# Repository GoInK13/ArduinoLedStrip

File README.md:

# ArduinoLedStrip
Arduino PCB to control LED strip RGB, addressable or not, with 1 IR remote, 1 pot and 2 push buttons.

**Kicad information**
This project is made using KiCad Version: 4.0.7-e2-6376~58~ubuntu14.04.1.

**Arduino information**
You need the library "RobotIRremote" in your libraries folder. I also modified "TDK2" to "12" in my arduino-1.6.9/libraries/RobotIRremote/src/IRremoteTools.cpp file.

**Component list**
The Arduino used is an ATmega328P Nano V3.
The DC 12V connector is a 5.5mm×2.1mm DC Power Supply Female Jack Socket.
The 6 transistors used are IRFZ44N Transistor N-Channel.
The polarized power capacitor is a 10µF, with a diameter egal to 8.0mm, and a pitch of 3.5mm.
SW1 and SW2 are Push Button DIP P4.
The potentiometer is a PTV09A from Bourns.
The IR receiver is a TSOP4838.
All pin header used have a pitch of 2.54mm.
All resistors are 0603 handsoldering (1kΩ).
Wemos : D1 mini

**Thanks**
Thanks to jerome-labidurie on GitHub for his d1_mini library. (Wemos)
https://github.com/jerome-labidurie/d1_mini_kicad.git

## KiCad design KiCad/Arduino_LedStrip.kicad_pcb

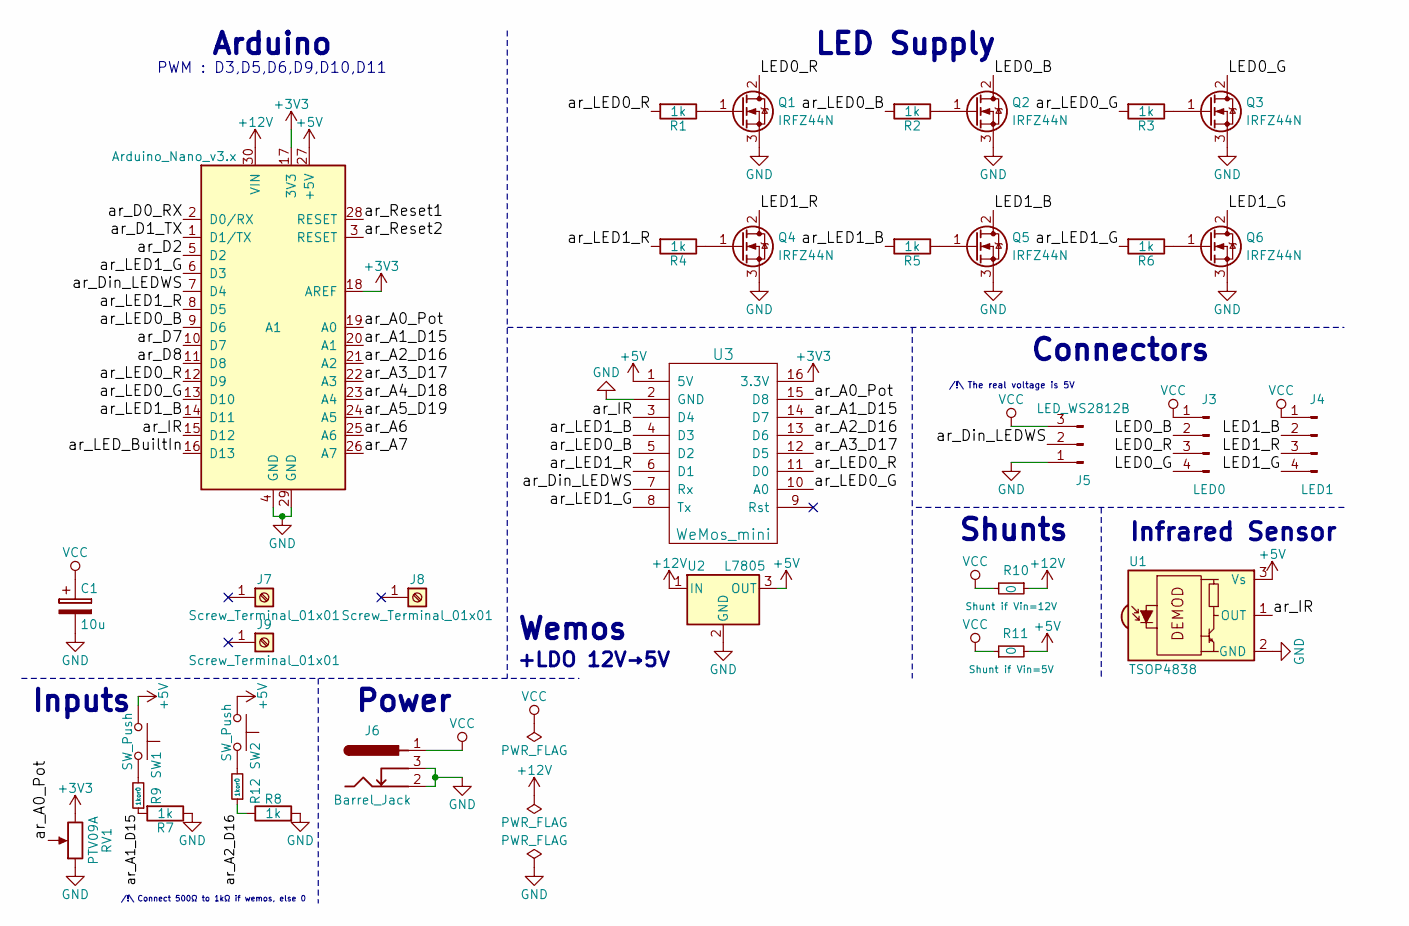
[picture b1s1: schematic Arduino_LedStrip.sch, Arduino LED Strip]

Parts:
A1: Arduino_Nano_v3.x; Arduino_Nano
C1: 10u; CP_Radial_D8.0mm_P3.50mm
J3: LED0; Pin_Header_Angled_1x04_Pitch2.54mm
J4: LED1; Pin_Header_Angled_1x04_Pitch2.54mm
J5: LED_WS2812B; Pin_Header_Angled_1x03_Pitch2.54mm
J6: Barrel_Jack; BARREL_JACK
J7, J8, J9: Screw_Terminal_01x01; MountingHole_3.2mm_M3
Q1, Q2, Q3, Q4, Q5, Q6: IRFZ44N; TO-220-3_Vertical
R1, R2, R3, R4, R5, R6, R7, R8: 1k; R_0603_HandSoldering
R9, R12: 1kor0; R_0603_HandSoldering
R10, R11: 0; R_Shunt
RV1: PTV09A; Potentiometer_Bourns_PTV09A-1_Horizontal
SW1, SW2: SW_Push; SW_PUSH_6mm_h13mm
U1: TSOP4838; IRReceiver_Vishay_MOLD-3pin
U2: L7805; TO-220-3_Vertical
U3: WeMos_mini; D1_mini_board

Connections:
+3V3: A1.17 (3V3), A1.18 (AREF), RV1.3, U3.16 (3.3V)
+5V: A1.27 (+5V), R11.2, SW1.1, SW2.1, U1.3 (Vs), U2.3 (OUT), U3.1 (5V)
+12V: A1.30 (VIN), R10.1, U2.1 (IN)
/LED0_B: J3.2, Q2.2 (D)
/LED0_G: J3.4, Q3.2 (D)
/LED0_R: J3.3, Q1.2 (D)
/LED1_B: J4.2, Q5.2 (D)
/LED1_G: J4.4, Q6.2 (D)
/LED1_R: J4.3, Q4.2 (D)
/ar_A0_Pot: A1.19 (A0), RV1.2, U3.15 (D8)
/ar_A1_D15: A1.20 (A1), R7.2, R9.1, U3.14 (D7)
/ar_A2_D16: A1.21 (A2), R8.1, R12.1, U3.13 (D6)
/ar_A3_D17: A1.22 (A3), U3.12 (D5)
/ar_A4_D18: A1.23 (A4)
/ar_A5_D19: A1.24 (A5)
/ar_A6: A1.25 (A6)
/ar_A7: A1.26 (A7)
/ar_D0_RX: A1.2 (D0/RX)
/ar_D1_TX: A1.1 (D1/TX)
/ar_D2: A1.5 (D2)
/ar_D7: A1.10 (D7)
/ar_D8: A1.11 (D8)
/ar_Din_LEDWS: A1.7 (D4), J5.2, U3.7 (Rx)
/ar_IR: A1.15 (D12), U1.1 (OUT), U3.3 (D4)
/ar_LED0_B: A1.9 (D6), R2.2, U3.5 (D2)
/ar_LED0_G: A1.13 (D10), R3.2, U3.10 (A0)
/ar_LED0_R: A1.12 (D9), R1.2, U3.11 (D0)
/ar_LED1_B: A1.14 (D11), R5.2, U3.4 (D3)
/ar_LED1_G: A1.6 (D3), R6.2, U3.8 (Tx)
/ar_LED1_R: A1.8 (D5), R4.2, U3.6 (D1)
/ar_LED_BuiltIn: A1.16 (D13)
/ar_Reset1: A1.28 (RESET)
/ar_Reset2: A1.3 (RESET)
GND: A1.4 (GND), A1.29 (GND), C1.2, J5.1, J6.2, J6.3, Q1.3 (S), Q2.3 (S), Q3.3 (S), Q4.3 (S), Q5.3 (S), Q6.3 (S), R7.1, R8.2, RV1.1, U1.2 (GND), U2.2 (GND), U3.2 (GND)
unnamed: Q1.1 (G), R1.1
unnamed: Q2.1 (G), R2.1
unnamed: Q3.1 (G), R3.1
unnamed: Q4.1 (G), R4.1
unnamed: Q5.1 (G), R5.1
unnamed: Q6.1 (G), R6.1
unnamed: R9.2, SW1.2
unnamed: R12.2, SW2.2
VCC: C1.1, J3.1, J4.1, J5.3, J6.1, R10.2, R11.1

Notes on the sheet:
PWM : D3,D5,D6,D9,D10,D11
Power
Inputs
Arduino
LED Supply
Connectors
Infrared Sensor
/!\ The real voltage is 5V
Wemos
+LDO 12V→5V
Shunts
/!\ Connect 500Ω to 1kΩ if wemos, else 0

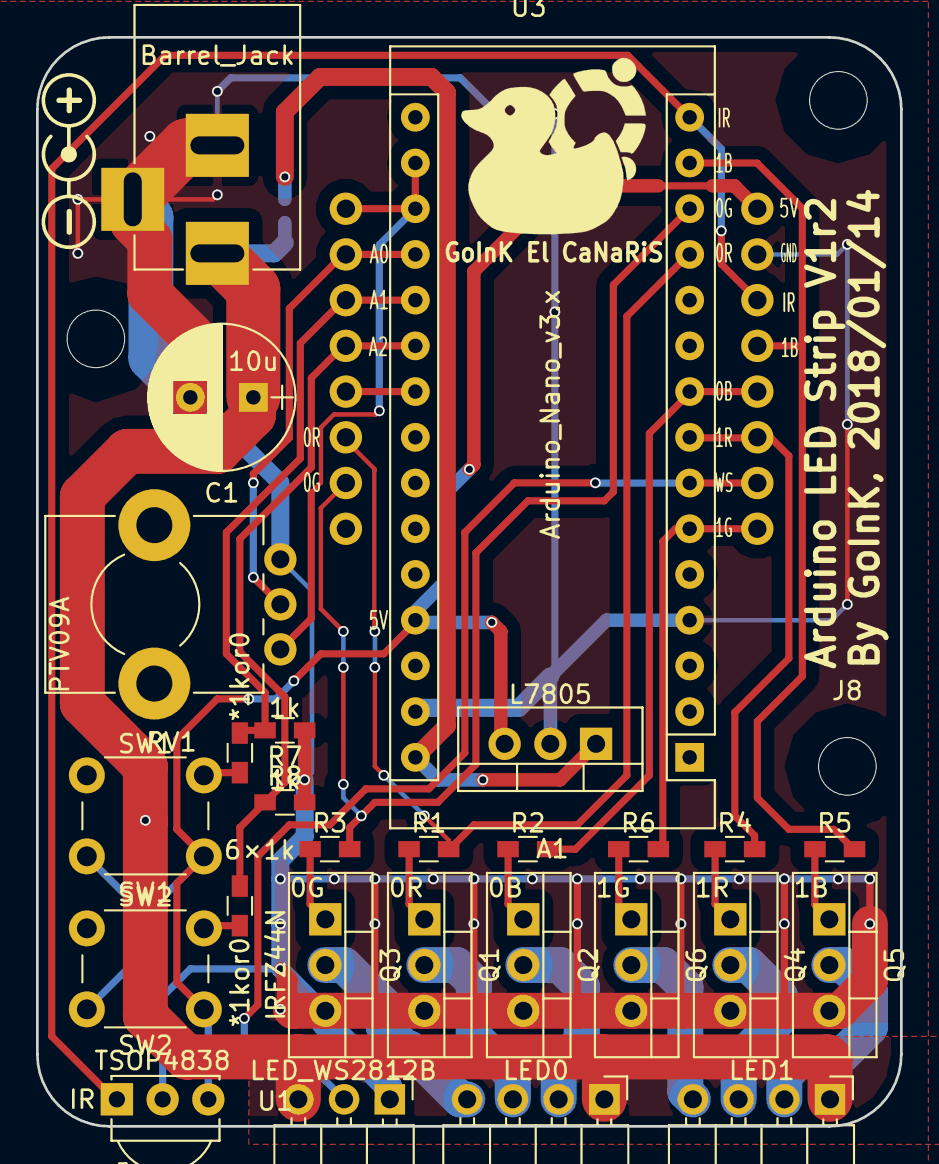
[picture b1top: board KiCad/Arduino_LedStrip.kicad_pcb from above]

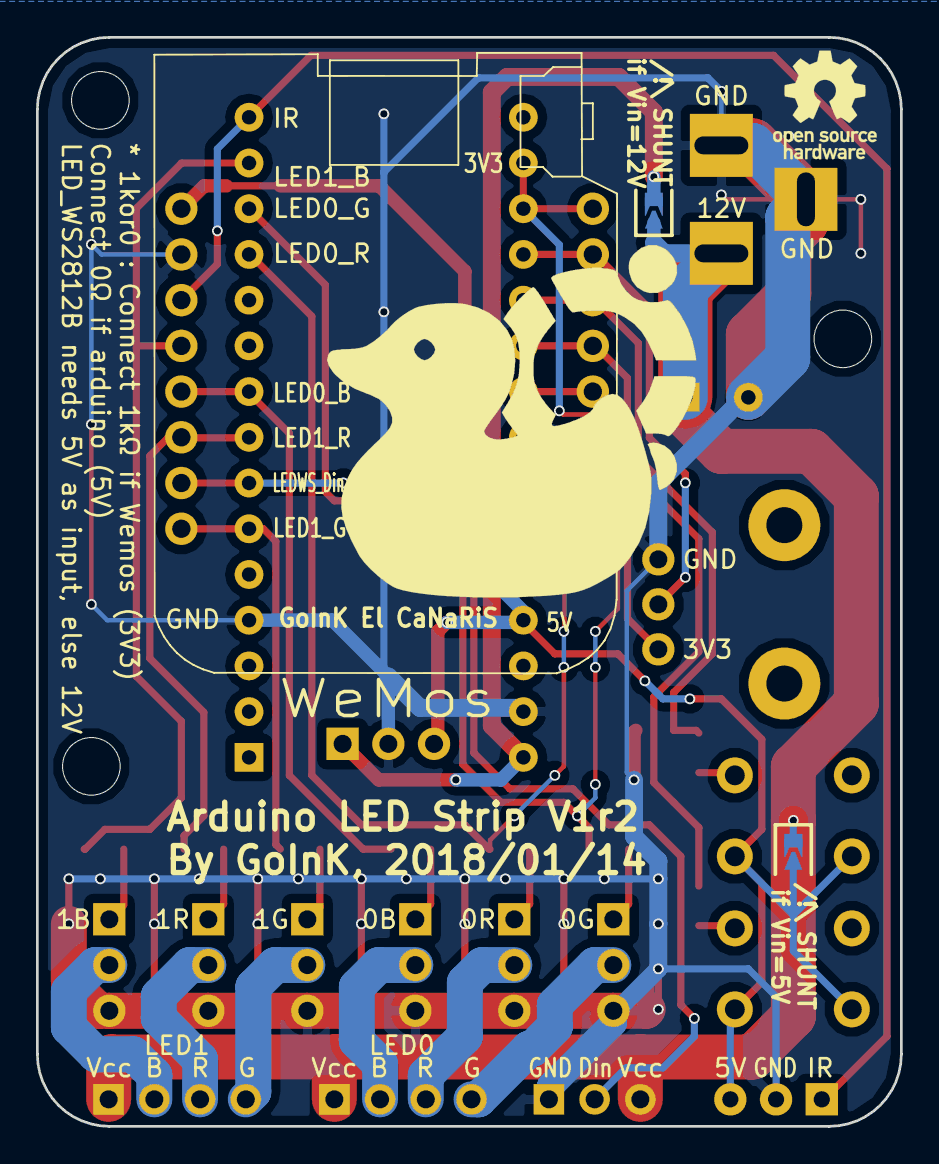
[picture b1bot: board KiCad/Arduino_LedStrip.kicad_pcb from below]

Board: 2 copper layers, 48.0 x 60.5 mm, 33 parts (2 on the bottom side), 31 nets.

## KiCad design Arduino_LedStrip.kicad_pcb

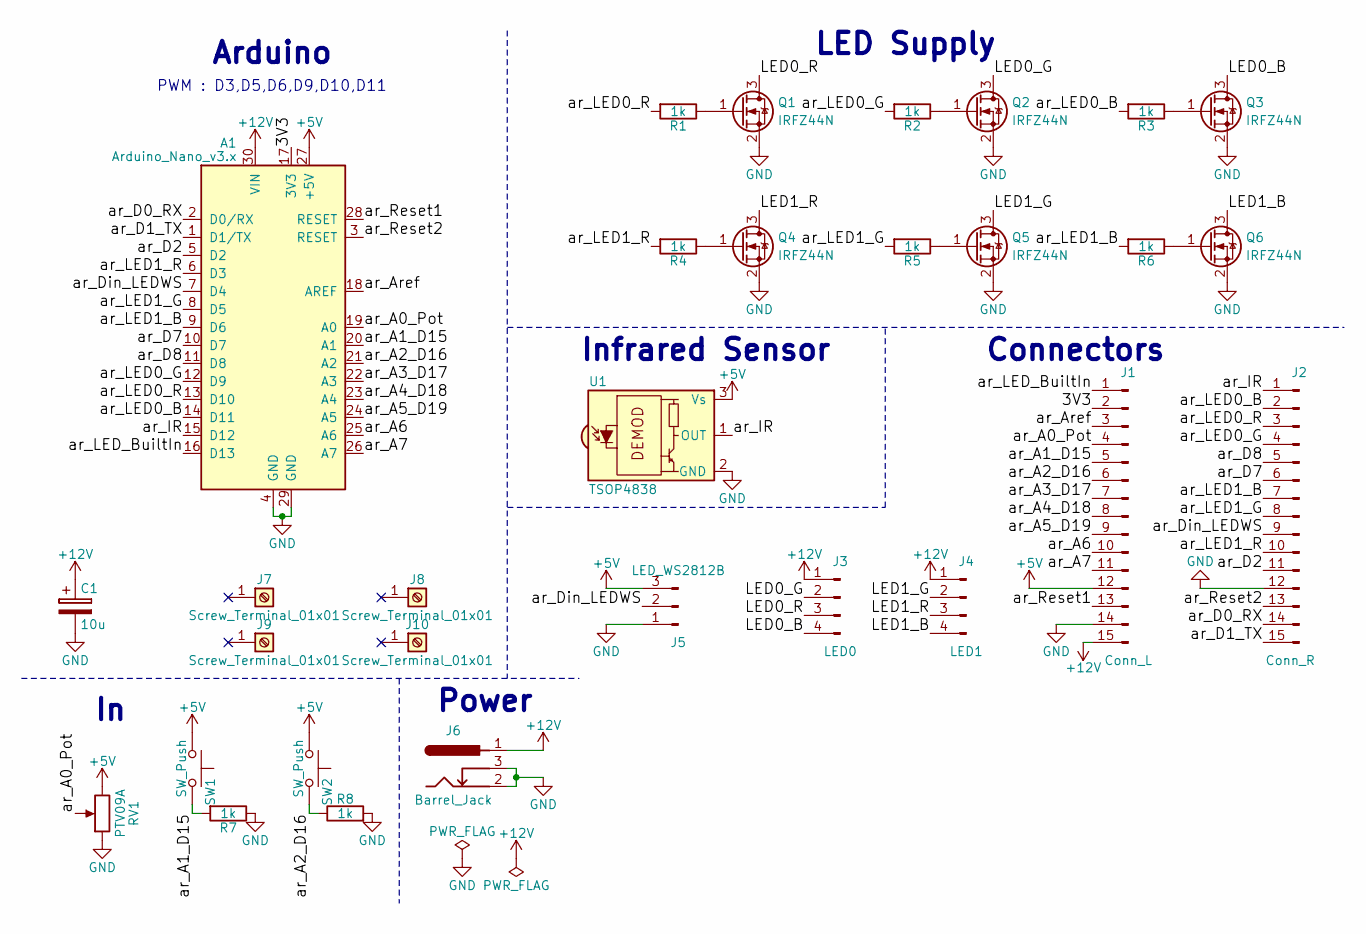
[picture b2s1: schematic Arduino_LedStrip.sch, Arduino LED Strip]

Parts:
A1: Arduino_Nano_v3.x; Arduino_Nano
C1: 10u; CP_Radial_D8.0mm_P3.50mm
J1: Conn_L; Pin_Header_Straight_1x15_Pitch2.54mm
J2: Conn_R; Pin_Header_Straight_1x15_Pitch2.54mm
J3: LED0; Pin_Header_Angled_1x04_Pitch2.54mm
J4: LED1; Pin_Header_Angled_1x04_Pitch2.54mm
J5: LED_WS2812B; Pin_Header_Angled_1x03_Pitch2.54mm
J6: Barrel_Jack; BARREL_JACK
J7, J8, J9, J10: Screw_Terminal_01x01; MountingHole_3.2mm_M3
Q1, Q2, Q3, Q4, Q5, Q6: IRFZ44N; TO-220-3_Vertical
R1, R2, R3, R4, R5, R6, R7, R8: 1k; R_0603_HandSoldering
RV1: PTV09A; Potentiometer_Bourns_PTV09A-1_Horizontal
SW1, SW2: SW_Push; SW_PUSH_6mm_h13mm
U1: TSOP4838; IRReceiver_Vishay_MOLD-3pin

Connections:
+5V: A1.27 (+5V), J1.12, J5.3, RV1.3, SW1.1, SW2.1, U1.3 (Vs)
+12V: A1.30 (VIN), C1.1, J1.15, J3.1, J4.1, J6.1
/3V3: A1.17 (3V3), J1.2
/LED0_B: J3.4, Q3.3 (D)
/LED0_G: J3.2, Q2.3 (D)
/LED0_R: J3.3, Q1.3 (D)
/LED1_B: J4.4, Q6.3 (D)
/LED1_G: J4.2, Q5.3 (D)
/LED1_R: J4.3, Q4.3 (D)
/ar_A0_Pot: A1.19 (A0), J1.4, RV1.2
/ar_A1_D15: A1.20 (A1), J1.5, R7.2, SW1.2
/ar_A2_D16: A1.21 (A2), J1.6, R8.1, SW2.2
/ar_A3_D17: A1.22 (A3), J1.7
/ar_A4_D18: A1.23 (A4), J1.8
/ar_A5_D19: A1.24 (A5), J1.9
/ar_A6: A1.25 (A6), J1.10
/ar_A7: A1.26 (A7), J1.11
/ar_Aref: A1.18 (AREF), J1.3
/ar_D0_RX: A1.2 (D0/RX), J2.14
/ar_D1_TX: A1.1 (D1/TX), J2.15
/ar_D2: A1.5 (D2), J2.11
/ar_D7: A1.10 (D7), J2.6
/ar_D8: A1.11 (D8), J2.5
/ar_Din_LEDWS: A1.7 (D4), J2.9, J5.2
/ar_IR: A1.15 (D12), J2.1, U1.1 (OUT)
/ar_LED0_B: A1.14 (D11), J2.2, R3.2
/ar_LED0_G: A1.12 (D9), J2.4, R2.2
/ar_LED0_R: A1.13 (D10), J2.3, R1.2
/ar_LED1_B: A1.9 (D6), J2.7, R6.2
/ar_LED1_G: A1.8 (D5), J2.8, R5.2
/ar_LED1_R: A1.6 (D3), J2.10, R4.2
/ar_LED_BuiltIn: A1.16 (D13), J1.1
/ar_Reset1: A1.28 (RESET), J1.13
/ar_Reset2: A1.3 (RESET), J2.13
GND: A1.4 (GND), A1.29 (GND), C1.2, J1.14, J2.12, J5.1, J6.2, J6.3, Q1.2 (S), Q2.2 (S), Q3.2 (S), Q4.2 (S), Q5.2 (S), Q6.2 (S), R7.1, R8.2, RV1.1, U1.2 (GND)
unnamed: Q1.1 (G), R1.1
unnamed: Q2.1 (G), R2.1
unnamed: Q3.1 (G), R3.1
unnamed: Q4.1 (G), R4.1
unnamed: Q5.1 (G), R5.1
unnamed: Q6.1 (G), R6.1

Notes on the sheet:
PWM : D3,D5,D6,D9,D10,D11
Power
Arduino
LED Supply
Connectors
Infrared Sensor

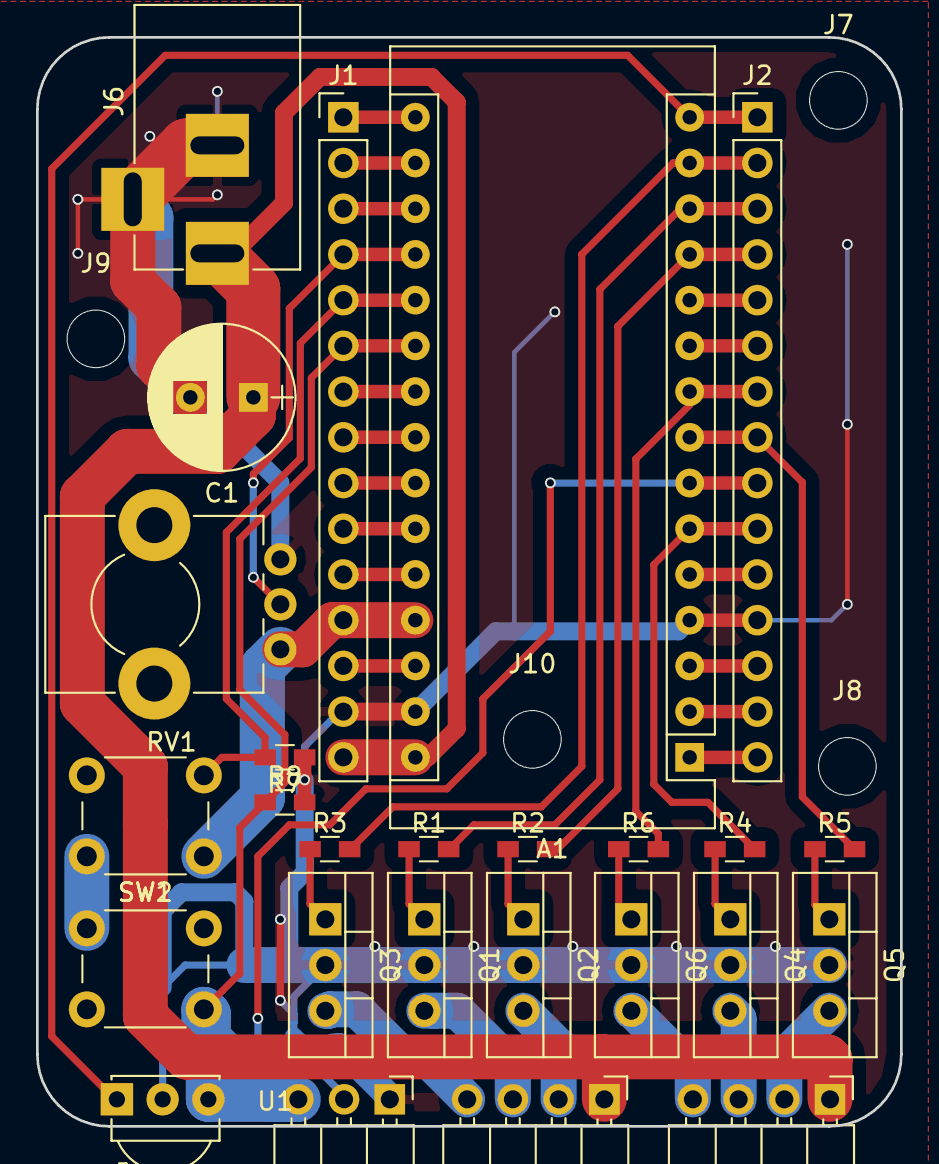
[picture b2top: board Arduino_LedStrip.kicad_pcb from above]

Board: 2 copper layers, 48.0 x 60.5 mm, 30 parts (0 on the bottom side), 41 nets.

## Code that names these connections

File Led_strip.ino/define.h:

#define IR_LG_RATIO	0x20DF9E61
#define IR_LG_AD		 0x20DF8976
#define IR_LG_TEXT	 0x20DF04FB
#define IR_LG_TOPT	 0x20DF847B
#define IR_LG_SUBTITLE 0x20DF9C63
#define IR_LG_STOP	 0x20DF8D72
#define IR_LG_PLAY	 0x20DF0DF2
#define IR_LG_PAUSE	0x20DF5DA2
#define IR_LG_PREV	 0x20DFF10E
#define IR_LG_NEXT	 0x20DF718E
#define IR_LG_SIMPLX 0x20DF7E81
#define IR_LG_RED		0x20DF4EB1
#define IR_LG_GREEN	0x20DF8E71
#define IR_LG_BLUE	 0x20DF8679
#define IR_LG_YELL	 0x20DFC639
//IR Receiver
#define IR_RECV_PIN 12
//LEDs
#define LEDWS_Din 4
#define LED0_R    10
#define LED0_G    11
#define LED0_B    9
#define LED1_R    3
#define LED1_G    6
#define LED1_B    5
//#define LED_BUILTIN 13  //Good reception IR
//Buttons
#define POT   A0   //Analog
#define BUTTON0   15		//Used to change mode
#define BUTTON1   16		//Used to set mode

#define BUT_MODE BUTTON0
#define BUT_SET BUTTON1

#define TURN_OFF	0
#define TURN_RED	1
#define TURN_GREEN	2
#define TURN_YELLOW	3
#define TURN_BLUE	4
#define TURN_PINK	5
#define TURN_TURQ	6
#define TURN_WHITE	7

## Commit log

2017-11-08 Update README.md
    First init of README
2017-11-16 End of schematic. First placement.
2017-11-23 Routing PCB
2017-11-24 Update routing.
2017-11-24 Rotate SW1 and SW2.
2017-11-29 Finish routing. Rearrange folders. Add Arduino folder with sketch.
2017-12-10 Draft Arduino INO.
2017-12-10 Change folder Arduino
2017-12-17 Update schematic. Change NMOS_GSD to GDS (TO220). Change 5V IR
2017-12-17 Update names. Add the 3 others LED
2017-12-31 Remove IR_RECEIVER which block D3 (LED1_R)
2018-01-03 Change color name. Add mode fade, and jump. Work on mode night
2018-01-06 Format all.
2018-01-08 Correct some bugs. Work on mode 4 blinks.
2018-01-14 Change mode when simple click during animation. Show old value in mode 4 when in settings.
2018-01-14 Add possibility to use a 5V or 12V power. Create new gerbers
2018-01-14 Update silks bot
2018-01-15 Update folder paths. Add Wemos.
2018-01-16 Add second settings to change brightness in mode 1, 2 and 3
2018-05-10 Change silks : 5V bot to 3V3.
2018-09-03 Add 3D compatible KiCad5
2018-09-04 Add freecad box.
2018-09-11 Need hole for bottom.
2018-09-11 Hole from LED done.
2018-09-14 Up 3D : Add Arduino Nano.
2019-08-30 Add stl file
2022-03-06 Add files via upload
    Add shematic pdf
